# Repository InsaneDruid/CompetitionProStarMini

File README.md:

# CompetitionProStarMini
A replacement PCB for the Competition Pro Mini and Pro Star Mini (with autofire) Joysticks to easily replace failing microswitches with modern parts. 

The Saia-Burgess F4T7-UL Microswitches used in this design provide up to 10 000 000 cycles of operation and allow the original stick gate to remain in place, giving the best overall experience.

A bent piece of copper wire can be used to further secure the directional switches to the pcb, using the provided mounting holes.

[Schematic](https://github.com/InsaneDruid/CompetitionProStarMini/blob/main/competitionProStarMini.pdf "Schematic")  

[Bill of Materials](https://htmlpreview.github.io/?https://github.com/InsaneDruid/CompetitionProStarMini/blob/main/bom/competitionProStarMini_bom.html "Bill of Materials")

## The License
This work is licensed under a Creative Commons Attribution-ShareAlike 4.0 International License.  
See https://creativecommons.org/licenses/by-sa/4.0/.

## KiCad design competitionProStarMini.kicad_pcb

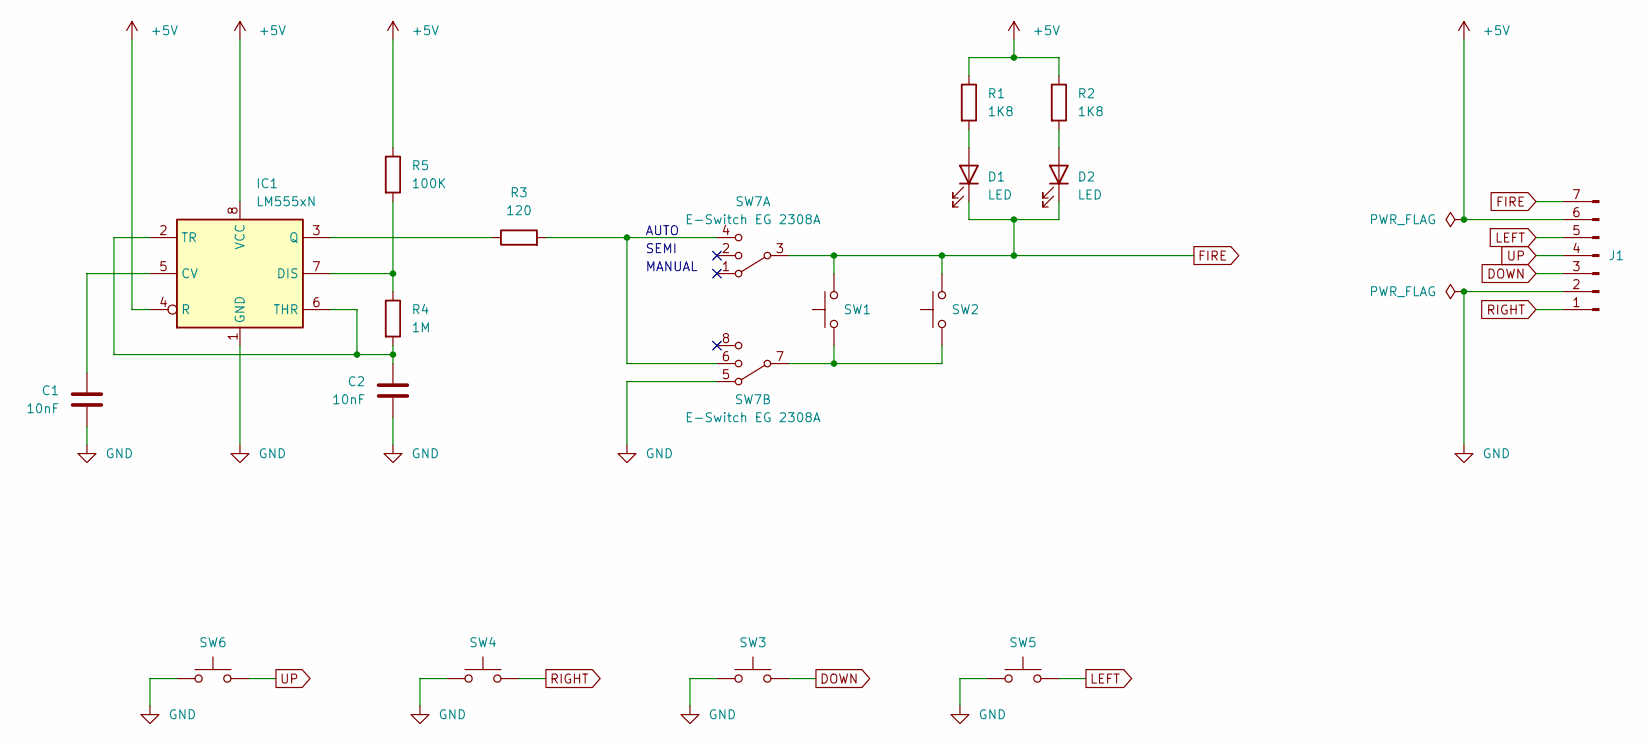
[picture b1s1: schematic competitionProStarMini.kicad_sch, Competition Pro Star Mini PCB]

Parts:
C1: 10nF; C_Disc_D3.0mm_W1.6mm_P2.50mm
C2: 10nF; C_Rect_L4.0mm_W2.5mm_P2.50mm
D1, D2: LED; LED_D3.0mm
IC1: LM555xN; DIP-8_W7.62mm_LongPads
J1: Conn_01x06_Pin; PinHeader_1x07_P2.54mm_Vertical
R1, R2: 1K8; R_Axial_DIN0207_L6.3mm_D2.5mm_P10.16mm_Horizontal
R3: 120; R_Axial_DIN0207_L6.3mm_D2.5mm_P10.16mm_Horizontal
R4: 1M; R_Axial_DIN0207_L6.3mm_D2.5mm_P10.16mm_Horizontal
R5: 100K; R_Axial_DIN0207_L6.3mm_D2.5mm_P10.16mm_Horizontal
SW1, SW2: Saia-Burgess_F4T7-UL
SW3, SW4, SW5, SW6: Saia-Burgess_F4T7-UL; Saia-Burgess_F4T7-UL_lying
SW7: E-Switch EG 2308A; EG2308

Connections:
+5V: IC1.4 (R), IC1.8 (VCC), J1.6, R1.1, R2.1, R5.1
DOWN: J1.3, SW3.2
FIRE: D1.1 (K), D2.1 (K), J1.7, SW1.2, SW2.2, SW7.3
GND: C1.1, C2.1, IC1.1 (GND), J1.2, SW3.1, SW4.1, SW5.1, SW6.2, SW7.5
LEFT: J1.5, SW5.2
unnamed: D1.2 (A), R1.2
unnamed: D2.2 (A), R2.2
unnamed: C1.2, IC1.5 (CV)
unnamed: IC1.7 (DIS), R4.1, R5.2
unnamed: IC1.3 (Q), R3.1
unnamed: C2.2, IC1.2 (TR), IC1.6 (THR), R4.2
unnamed: R3.2, SW7.4, SW7.6
unnamed: SW1.1, SW2.1, SW7.7
RIGHT: J1.1, SW4.2
UP: J1.4, SW6.1

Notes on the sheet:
AUTO
SEMI
MANUAL

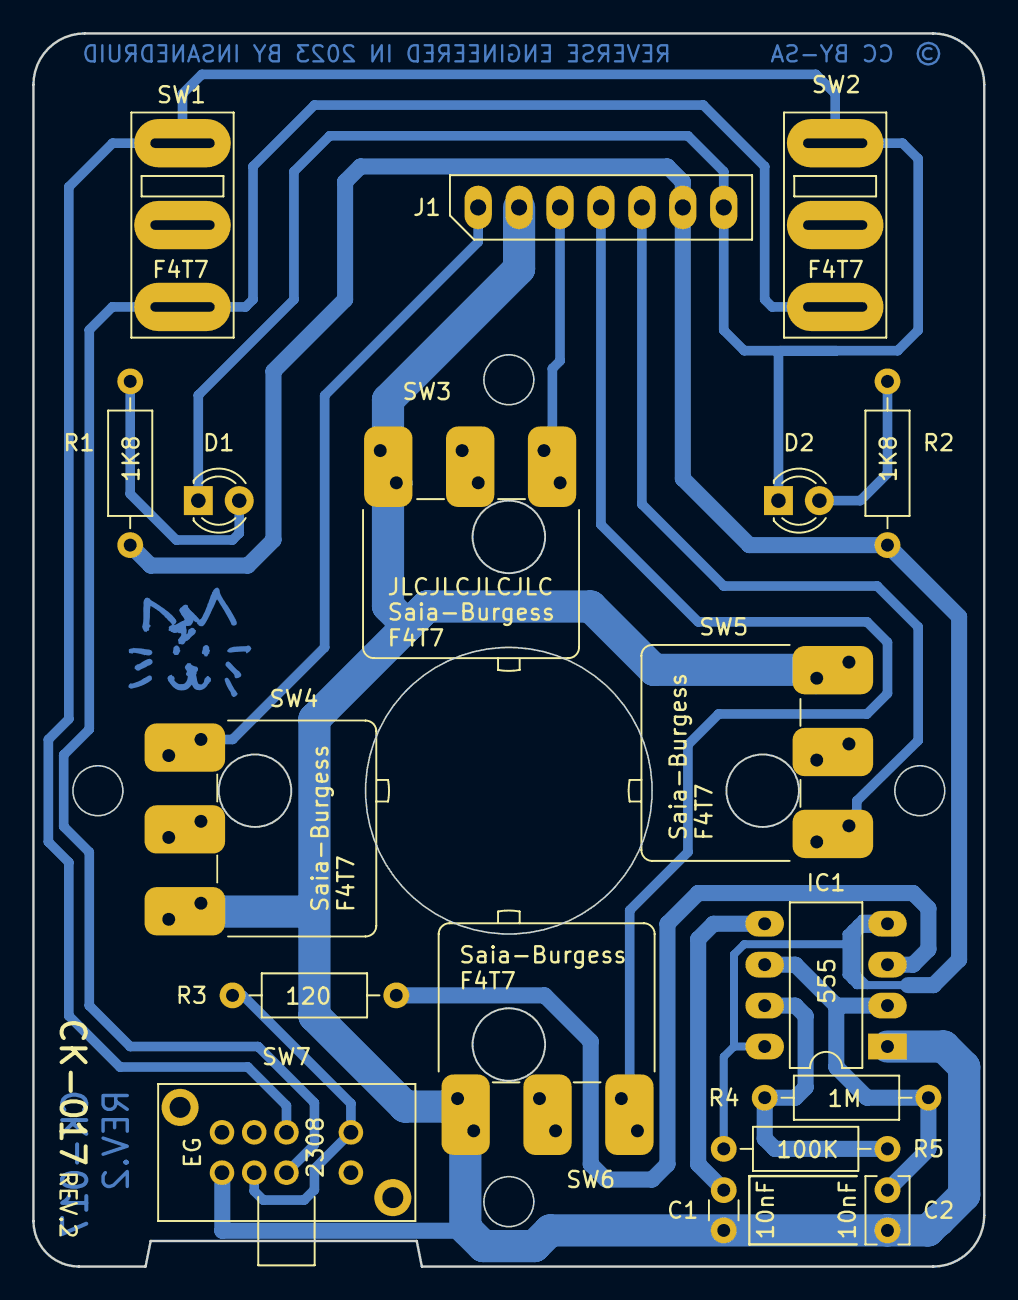
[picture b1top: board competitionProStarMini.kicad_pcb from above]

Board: 2 copper layers, 59.0 x 76.5 mm, 18 parts (0 on the bottom side), 15 nets.

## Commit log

2023-10-30 render image & fablayer cleanup
    cleaned up and overhauled the fab layer of the pcb
    added a slightly cleaner and bigger render image
2024-02-16 kicad drawing sheet fixes
    fixed license links in drawing sheets to match board prints, readme and project

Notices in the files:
competitionProStarMini.kicad_pcb:
License: CC BY-SA 4.0
CC BY-SA
